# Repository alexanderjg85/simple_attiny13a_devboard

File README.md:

# simple_attiny13a_devboard
A simple development board with an LED and GPIOs on Pin header, includes also ISP Header, Power supply with screw terminal.

## Project Structure
- **/hardware**: Contains the KiCad schematic and PCB layout files.
- **/firmware**: Contains the Microchip Studio 7 C/ASM source code.

## Programming Notes
- Designed for the **ATtiny13A** microcontroller.
- Programmed using **Atmel Studio 7** and an **AVRISP mkII** programmer.
- *Note:* The board requires an external power supply (e.g., 5V) during programming, as the AVRISP mkII does not supply power to the target VCC.

## License / Lizenz

This project is dual-licensed / Dieses Projekt ist dual-lizenziert:

* **Hardware (Schematic, PCB Layout):** Licensed under the [CERN Open Hardware Licence Version 2 - Permissive (CERN-OHL-P)](LICENSE_HARDWARE.md).
* **Software (Firmware, Example Code):** Licensed under the [MIT License](LICENSE).

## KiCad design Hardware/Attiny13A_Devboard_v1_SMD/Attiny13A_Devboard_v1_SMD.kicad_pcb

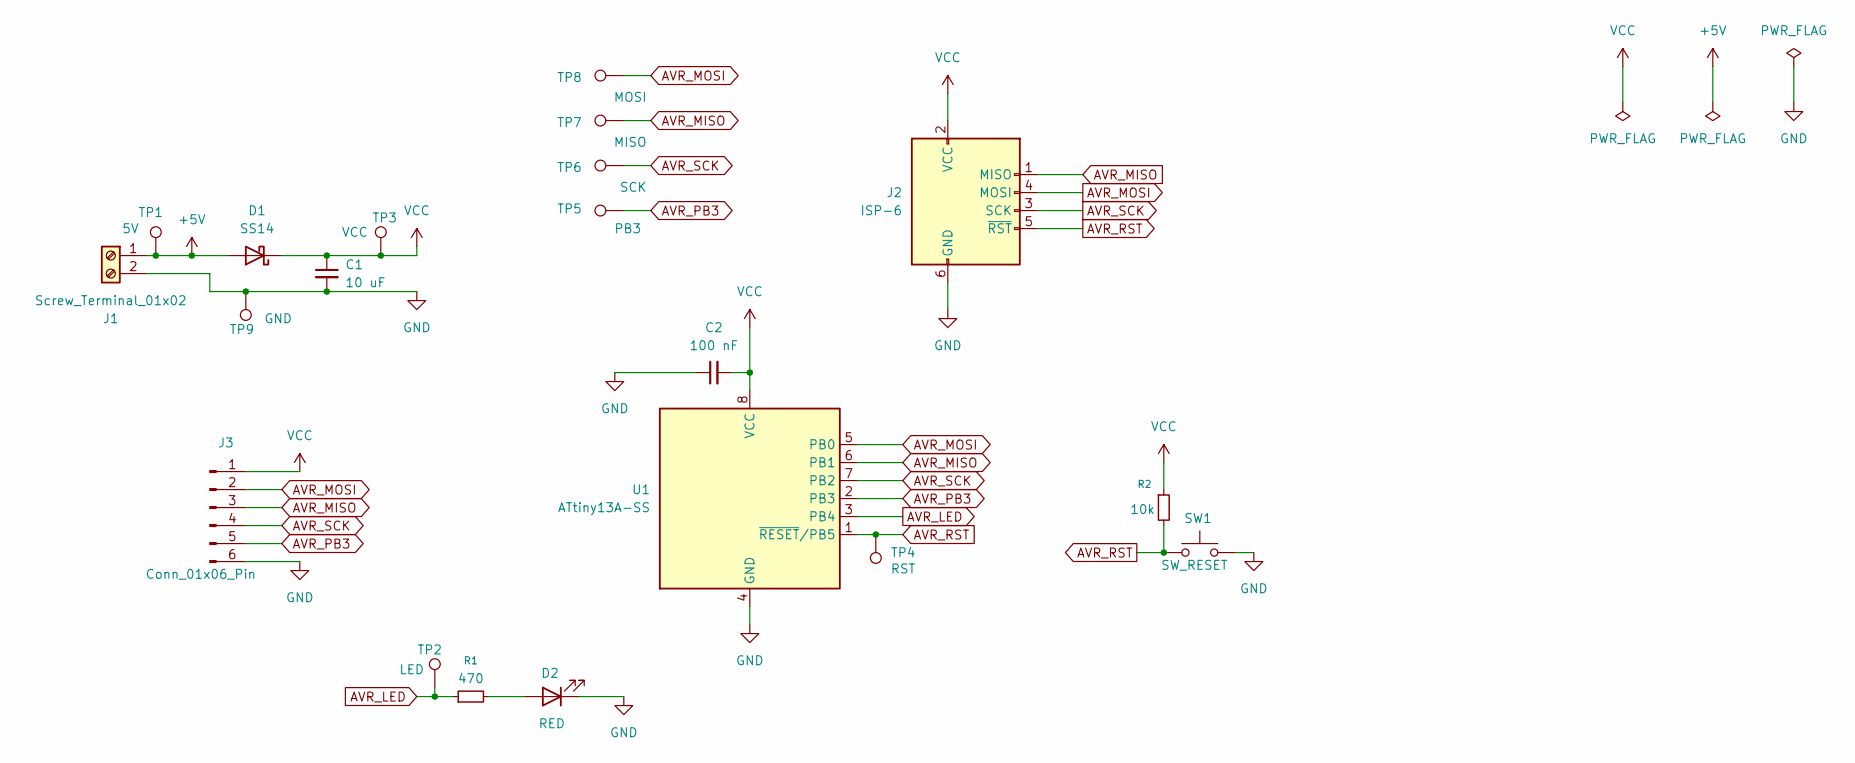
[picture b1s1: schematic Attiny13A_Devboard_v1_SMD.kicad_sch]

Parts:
C1: 10 uF; C_1206_3216Metric_Pad1.33x1.80mm_HandSolder
C2: 100 nF; C_1206_3216Metric_Pad1.33x1.80mm_HandSolder
D1: SS14; D_SMA_Handsoldering
D2: RED; LED_1206_3216Metric_Pad1.42x1.75mm_HandSolder
J1: Screw_Terminal_01x02; TerminalBlock_Phoenix_MKDS-1,5-2-5.08_1x02_P5.08mm_Horizont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
J2: ISP-6; PinHeader_2x03_P2.54mm_Vertical
J3: Conn_01x06_Pin; PinHeader_1x06_P2.54mm_Vertical
R1: 470; R_1206_3216Metric_Pad1.30x1.75mm_HandSolder
R2: 10k; R_1206_3216Metric_Pad1.30x1.75mm_HandSolder
SW1: SW_RESET; SW_SPST_PTS647_Sx38_Handsolder; MFR PN SWT0210-045026GSA
TP1: 5V; TestPoint_Pad_D1.5mm
TP2: LED; TestPoint_Pad_D1.5mm
TP3: VCC; TestPoint_Pad_D1.5mm
TP4: RST; TestPoint_Pad_D1.5mm
TP5: PB3; TestPoint_Pad_D1.5mm
TP6: SCK; TestPoint_Pad_D1.5mm
TP7: MISO; TestPoint_Pad_D1.5mm
TP8: MOSI; TestPoint_Pad_D1.5mm
TP9: GND; TestPoint_Pad_D1.5mm
U1: ATtiny13A-SS; SOIC-8_3.9x4.9mm_P1.27mm; MFR PN ATTINY13A-SSU

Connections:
+5V: D1.2 (A), J1.1, TP1.1 (1_1)
AVR_LED: R1.1, TP2.1 (1_1), U1.3 (PB4)
AVR_MISO: J2.1 (MISO), J3.3, TP7.1 (1_1), U1.6 (PB1)
AVR_MOSI: J2.4 (MOSI), J3.2, TP8.1 (1_1), U1.5 (PB0)
AVR_PB3: J3.5, TP5.1 (1_1), U1.2 (PB3)
AVR_RST: J2.5 (~RST), R2.2, SW1.1, TP4.1 (1_1), U1.1 (~RESET/PB5)
AVR_SCK: J2.3 (SCK), J3.4, TP6.1 (1_1), U1.7 (PB2)
GND: C1.2, C2.1, D2.1 (K), J1.2, J2.6 (GND), J3.6, SW1.2, TP9.1 (1_1), U1.4 (GND)
unnamed: D2.2 (A), R1.2
VCC: C1.1, C2.2, D1.1 (K), J2.2 (VCC), J3.1, R2.1, TP3.1 (1_1), U1.8 (VCC)

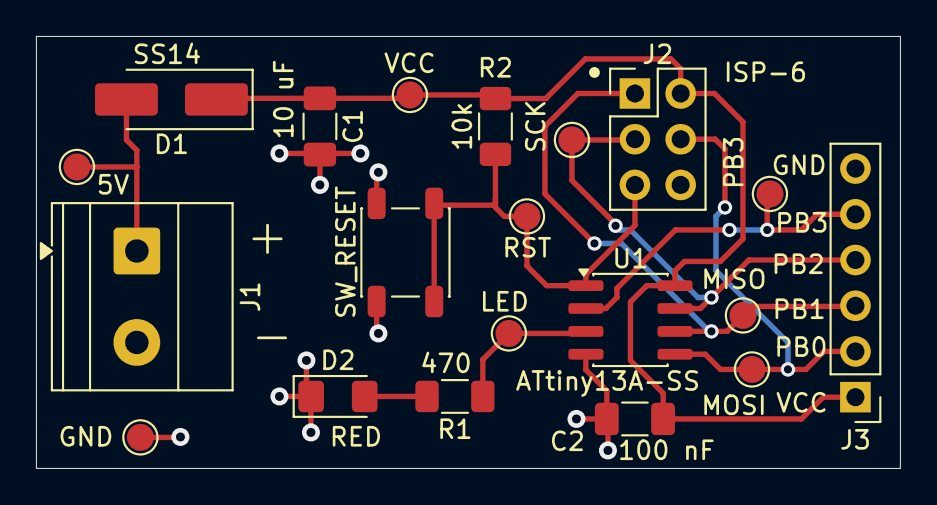
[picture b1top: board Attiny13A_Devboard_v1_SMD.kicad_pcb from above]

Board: 2 copper layers, 48.0 x 24.0 mm, 20 parts (0 on the bottom side), 10 nets.
